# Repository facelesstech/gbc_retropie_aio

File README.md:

# gbc_retropie_aio

rev A

gbc_retropie_aio

Blog post - https://facelesstech.wordpress.com/2020/10/24/gbc-retropie-aio/

Youtube - https://youtu.be/fNg7gt766WU

rev B

gbc_retropie_aio

Blog post - 

Youtube -

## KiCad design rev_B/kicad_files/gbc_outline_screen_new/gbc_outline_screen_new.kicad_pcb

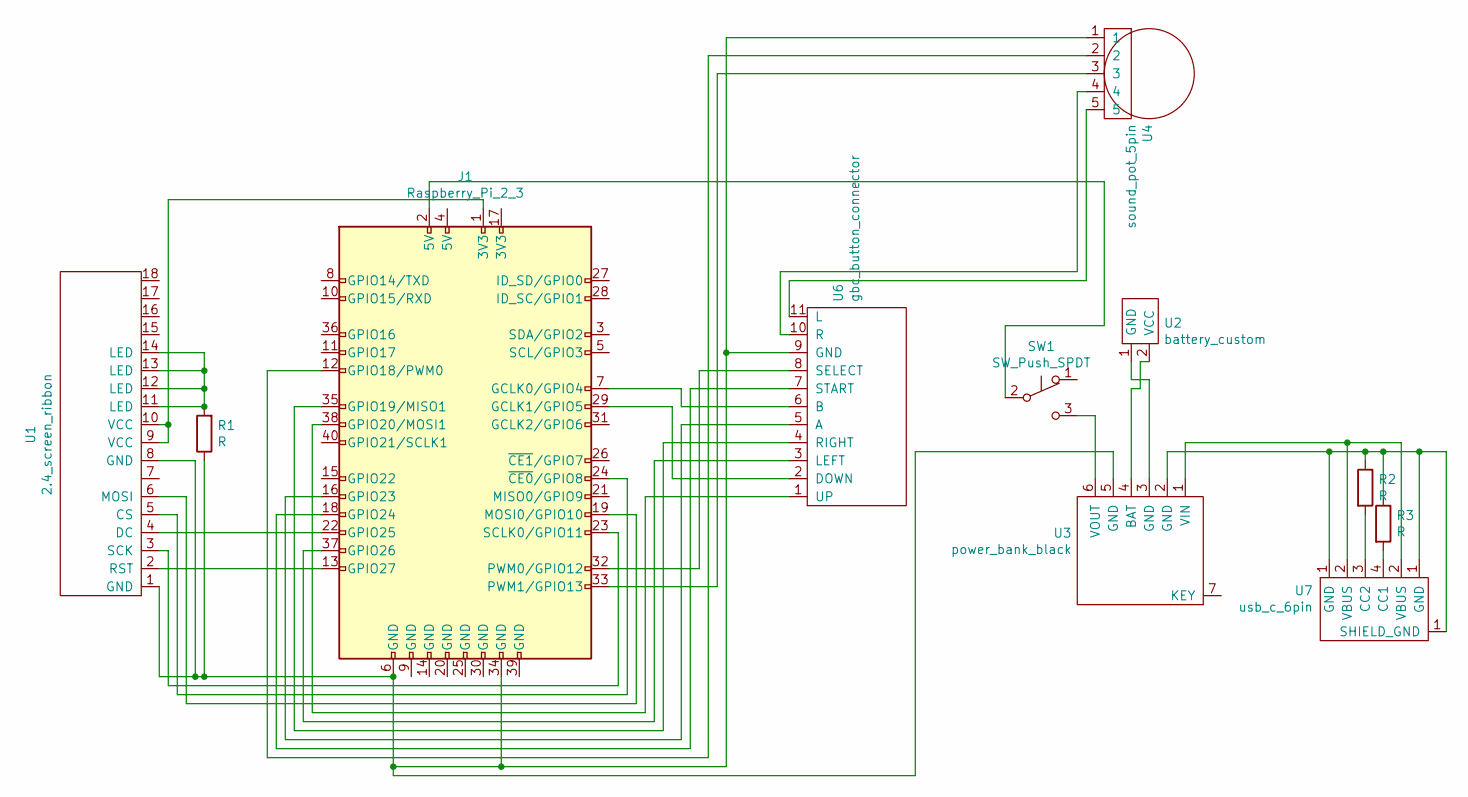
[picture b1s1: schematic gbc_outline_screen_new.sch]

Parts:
J1: Raspberry_Pi_2_3; raspberry_pi_gpio_SMD_outline_under_holes
R1, R2, R3: R; R_1206_3216Metric_Pad1.42x1.75mm_HandSolder
SW1: SW_Push_SPDT; 3_pin_switch_smd_side_mount
U1: 2.4_screen_ribbon; 2.4_screen_ribbon_breakout
U2: battery_custom; vcc_gnd_2pin_custom
U3: power_bank_black; power_bank_black_smd
U4: sound_pot_5pin; GBC_pot_custom
U6: gbc_button_connector; GBC_controller_side_basic
U7: usb_c_6pin; USB_C_6PIN_custom

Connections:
unnamed: J1.1 (3V3), U1.9 (VCC), U1.10 (VCC)
unnamed: J1.2 (5V), SW1.2 (B)
unnamed: J1.7 (GCLK0/GPIO4), U6.6 (B)
unnamed: J1.12 (GPIO18/PWM0), U4.2
unnamed: J1.13 (GPIO27), U1.2 (RST)
unnamed: J1.16 (GPIO23), U6.5 (A)
unnamed: J1.18 (GPIO24), U6.7 (START)
unnamed: J1.19 (MOSI0/GPIO10), U1.6 (MOSI)
unnamed: J1.22 (GPIO25), U1.4 (DC)
unnamed: J1.23 (SCLK0/GPIO11), U1.3 (SCK)
unnamed: J1.24 (~CE0~/GPIO8), U1.5 (CS)
unnamed: J1.29 (GCLK1/GPIO5), U6.2 (DOWN)
unnamed: J1.32 (PWM0/GPIO12), U6.8 (SELECT)
unnamed: J1.33 (PWM1/GPIO13), U4.3
unnamed: J1.6 (GND), J1.34 (GND), R1.1, U1.1 (GND), U1.8 (GND), U3.5 (GND), U4.1, U6.9 (GND)
unnamed: J1.35 (GPIO19/MISO1), U6.4 (RIGHT)
unnamed: J1.37 (GPIO26), U6.3 (LEFT)
unnamed: J1.38 (GPIO20/MOSI1), U6.1 (UP)
unnamed: R1.2, U1.11 (LED), U1.12 (LED), U1.13 (LED), U1.14 (LED)
unnamed: R2.1, R3.1, U3.2 (GND), U7.1 (GND)
unnamed: R2.2, U7.3 (CC2)
unnamed: R3.2, U7.4 (CC1)
unnamed: SW1.3 (C), U3.6 (VOUT)
unnamed: U2.1 (GND), U3.3 (GND)
unnamed: U2.2 (VCC), U3.4 (BAT)
unnamed: U3.1 (VIN), U7.2 (VBUS)
unnamed: U4.4, U6.10 (R)
unnamed: U4.5, U6.11 (L)

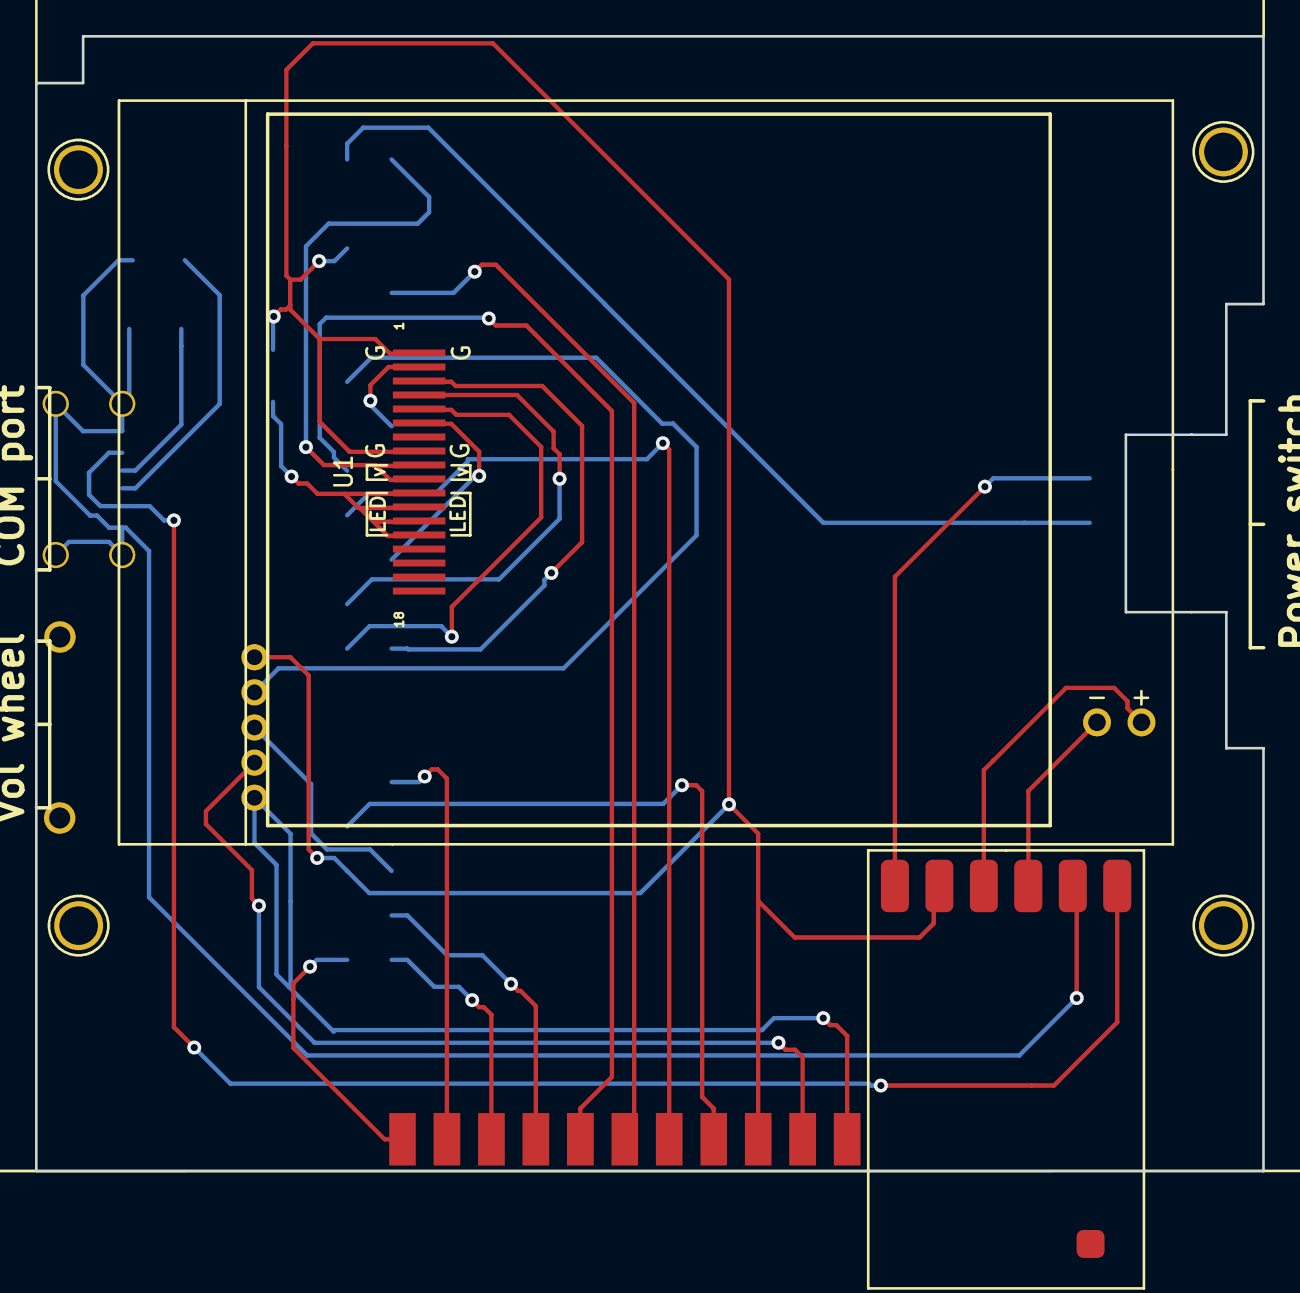
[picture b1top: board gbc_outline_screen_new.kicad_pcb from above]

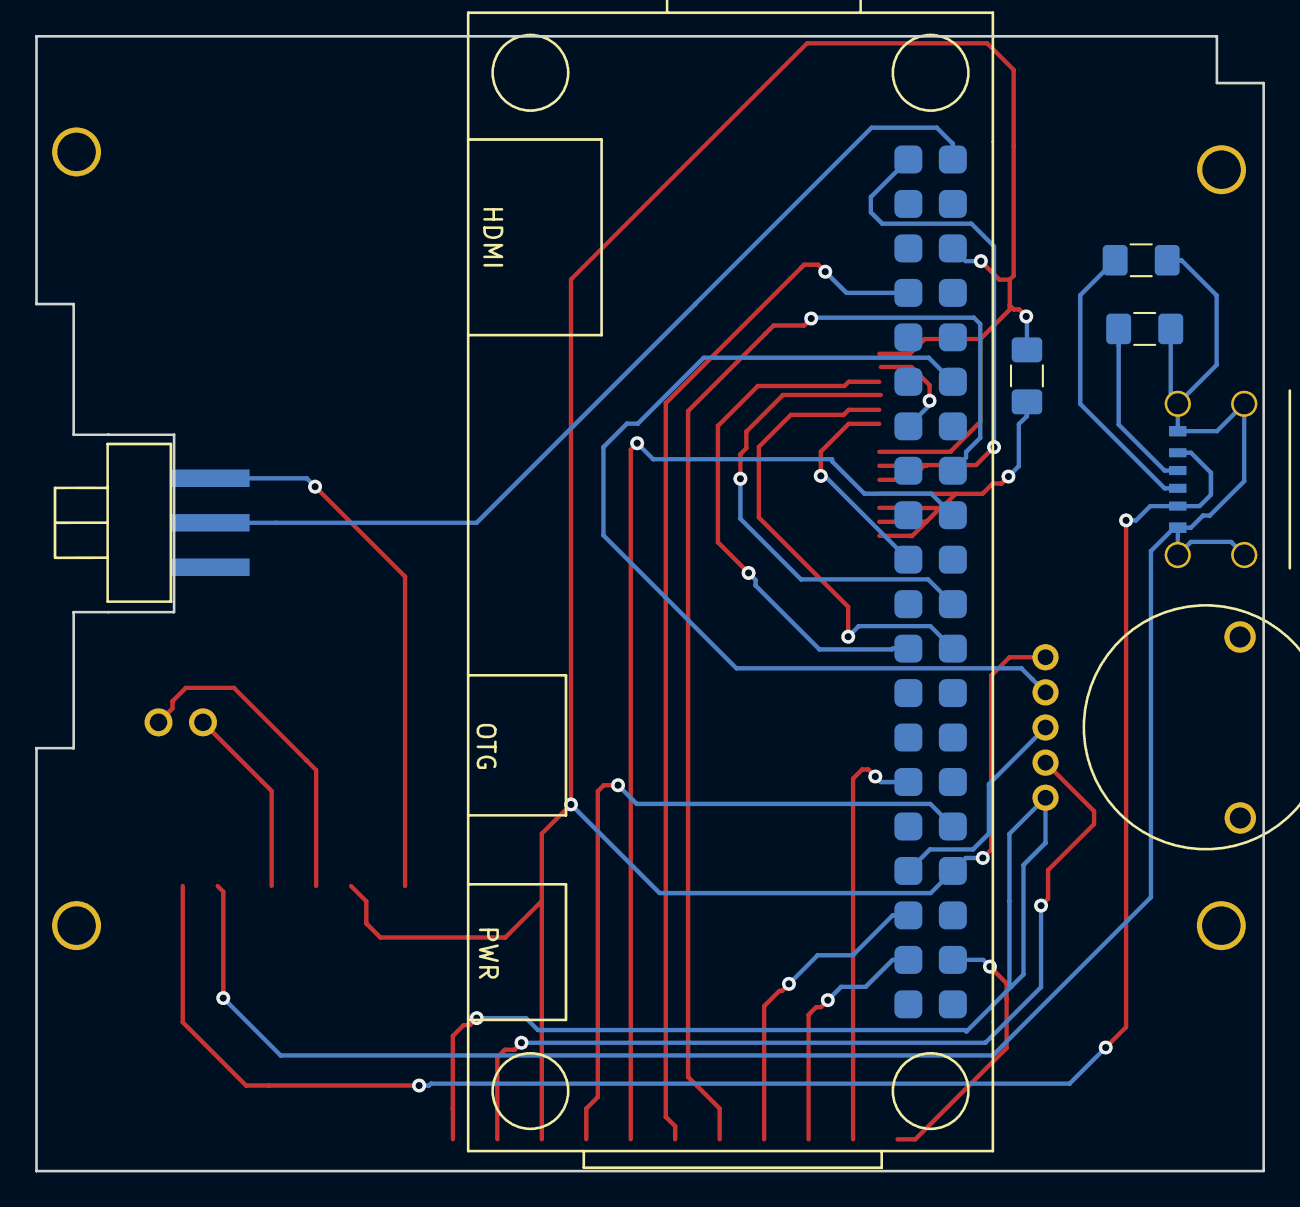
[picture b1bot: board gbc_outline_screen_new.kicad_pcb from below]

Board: 2 copper layers, 70.1 x 64.8 mm, 11 parts (7 on the bottom side), 28 nets.

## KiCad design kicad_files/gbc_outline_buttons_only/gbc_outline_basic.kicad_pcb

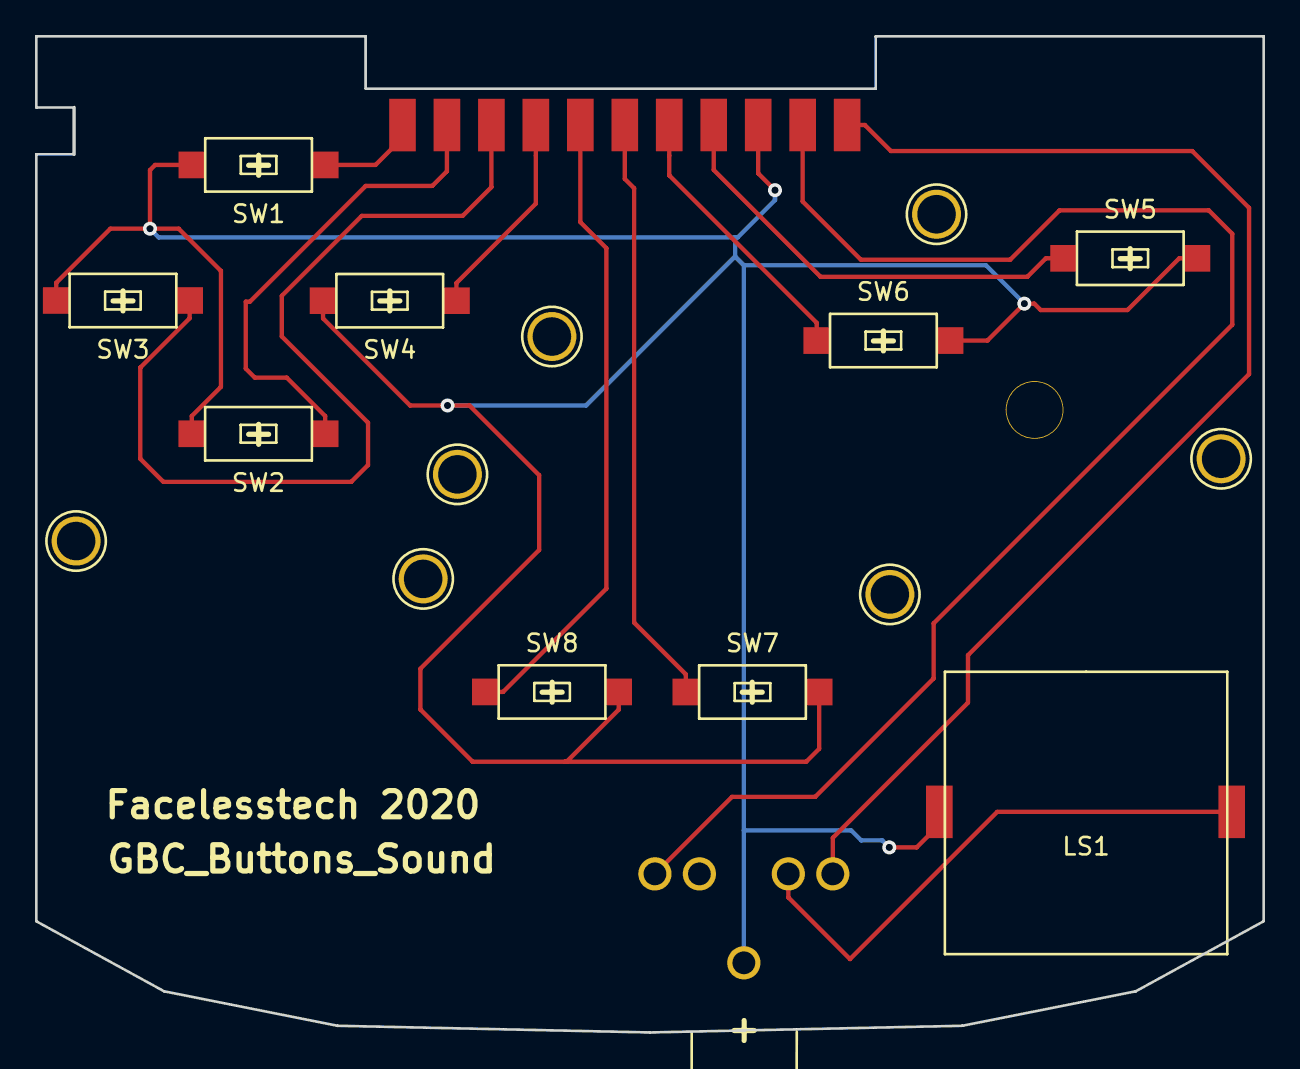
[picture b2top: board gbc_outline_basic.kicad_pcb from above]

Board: 2 copper layers, 70.1 x 56.9 mm, 11 parts (1 on the bottom side), 12 nets.

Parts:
LS1: Speaker; piezo_smd
SW1, SW2, SW3, SW4, SW5, SW6, SW7, SW8: SW_Push; SMD_2pin_button_custom
U1: audio_jack_5pin; 5_pin_3.5_jack
U2: gbc_button_connector; GBC_controller_side_basic

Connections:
unnamed: LS1.1, U1.3
unnamed: LS1.2, SW1.2, SW2.2, SW3.2, SW4.2, SW5.2, SW6.2, SW7.2, SW8.2, U1.1, U2.9
unnamed: SW1.1, U2.1
unnamed: SW2.1, U2.2
unnamed: SW3.1, U2.3
unnamed: SW4.1, U2.4
unnamed: SW5.1, U2.8
unnamed: SW6.1, U2.7
unnamed: SW7.1, U2.6
unnamed: SW8.1, U2.5
unnamed: U1.2, U2.11
unnamed: U1.5, U2.10

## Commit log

2020-10-24 3d printing files
2020-10-24 kicad files
2020-11-29 added links
2021-01-01 moved files
2021-01-01 added the files for the rev B
